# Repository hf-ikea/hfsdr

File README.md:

# https://github.com/hf-ikea/hfsdr
https://munin.uit.no/bitstream/handle/10037/19423/thesis.pdf --- ref\
https://www.analog.com/en/products/ad9641.pdf                --- main adc 14bit 80/155msps\
https://www.analog.com/en/products/ada4938-1.html            --- adc driver\
https://www.analog.com/en/products/adl5206.html              --- vga canidate\
https://www.analog.com/en/products/ad8331.html               --- vga canidate\
https://www.analog.com/en/products/ad9515.html               --- clk distrib

bpf\
vga\
antialias lpf 8th order chebyshev\
driver\
adc\
fpga fifo - lattice ecp5?\
ft60x\
usb phy

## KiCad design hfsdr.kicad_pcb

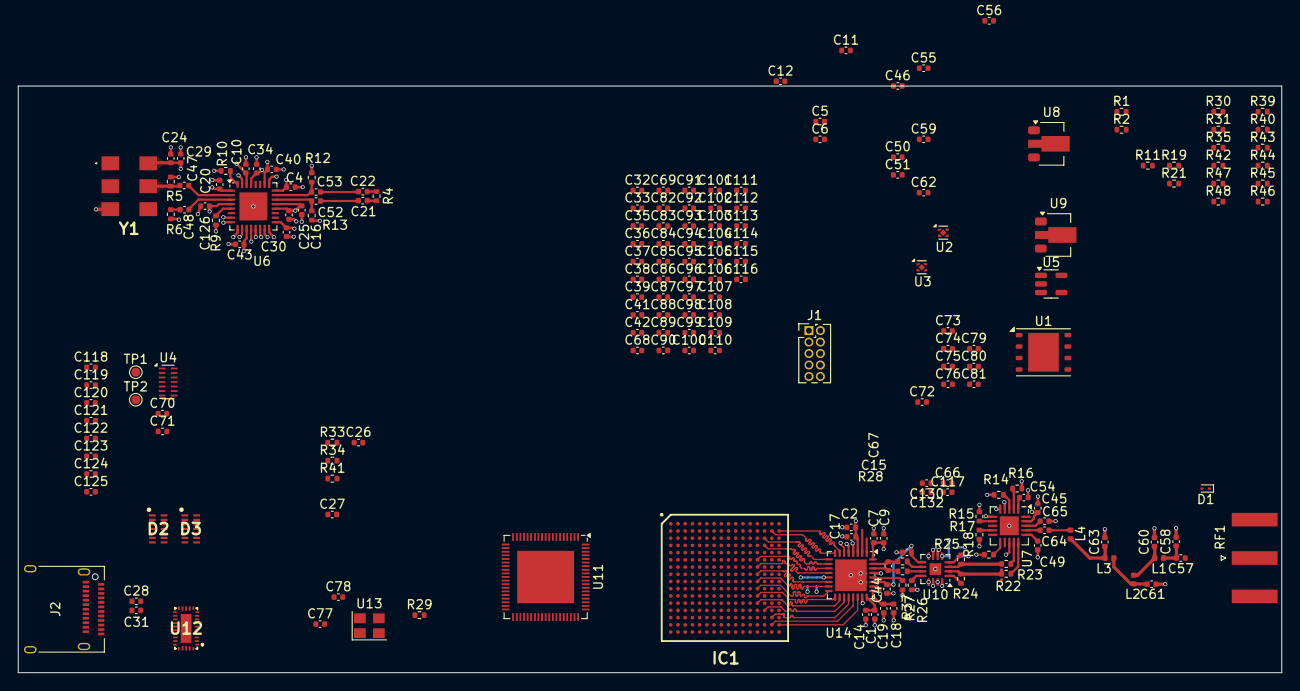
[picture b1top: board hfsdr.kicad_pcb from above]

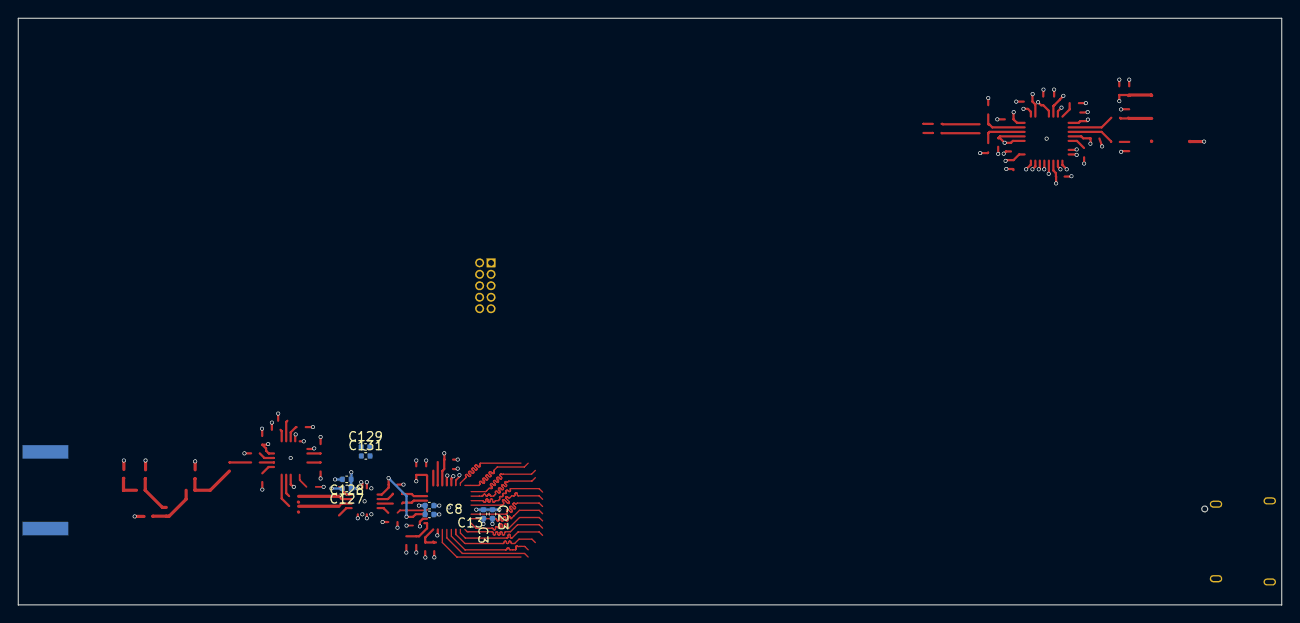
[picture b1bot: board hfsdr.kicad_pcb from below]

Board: 4 copper layers, 140.0 x 65.0 mm, 201 parts (8 on the bottom side), 170 nets.

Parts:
C1, C3, C4, C7, C10, C13, C15, C16, C17, C18, C20, C21, C22, C24, C25, C30, C34, C40, C43, C44, C45, C46, C49, C54, C79, C80, C81, C126: 0.1uF; C_0402_1005Metric
C2, C5, C6, C8, C9, C11, C12, C14, C19, C23, C29, C50, C51, C55, C59: 1uF; C_0402_1005Metric
C26, C28, C31, C70, C71, C72: 100n; C_0402_1005Metric
C27, C36, C41, C47, C48, C64, C65, C75, C76, C82, C92, C93, C94, C96, C98, C100, C102, C104, C106, C108, C110, C112, C114, C116, C117, C119, C121, C123, C125, C128, C131, C132: 0.1u; C_0402_1005Metric
C32, C33, C35, C37, C38, C39, C42, C68, C69, C83, C84, C85, C86, C87, C88, C89, C90, C91, C95, C97, C99, C101, C103, C105, C107, C109, C111, C113, C115, C118, C120, C122, C124: 10u; C_0402_1005Metric
C52, C53: 0.1n; C_0402_1005Metric
C56, C62: 2.2uF; C_0402_1005Metric
C57: 470n; C_0402_1005Metric
C58: 120p; C_0402_1005Metric
C60, C61: 200p; C_0402_1005Metric
C63: 160p; C_0402_1005Metric
C66, C127, C129, C130: 1n; C_0402_1005Metric
C67: 22pF; C_0402_1005Metric
C73: 100u; C_0402_1005Metric
C74: 4.7u; C_0402_1005Metric
C77, C78: 26p; C_0402_1005Metric
D1: ESD9B3.3ST5G; D_SOD-923
D2, D3: TPD4E05U06DQAR; SON50P135X350X55-14N
IC1: LFE5U-25F-6BG256C; BGA256C80P16X16_1400X1400X170
J1: JTAG; PinHeader_2x05_P1.27mm_Vertical
J2: GSB4D313302Y1HR; USB_C_Receptacle_Amphenol_12401610E4-2A
L1: 390n; L_0402_1005Metric
L2: 470n; L_0402_1005Metric
L3: 510n; L_0402_1005Metric
L4: 300n; L_0402_1005Metric
R1, R2, R9, R11, R14, R15, R16, R17, R18, R26, R37: 10k; R_0402_1005Metric
R4: 100; R_0402_1005Metric
R5, R6, R12, R13, R19: 50k; R_0402_1005Metric
R10: 4.12k; R_0402_1005Metric
R21: 25k; R_0402_1005Metric
R22, R23: 50; R_0402_1005Metric
R24, R25: 250; R_0402_1005Metric
R27, R28: 33; R_0402_1005Metric
R29: 1.6K 1%; R_0402_1005Metric
R30: 900k; R_0402_1005Metric
R31, R40, R43, R44, R45: 4.7k; R_0402_1005Metric
R33, R34, R41: 10K; R_0402_1005Metric
R35: 200k; R_0402_1005Metric
R39: 1.5k; R_0402_1005Metric
R42: 22; R_0402_1005Metric
R46: 120; R_0402_1005Metric
R47, R48: 0; R_0402_1005Metric
RF1: RFIN; SMA_Amphenol_132289_EdgeMount
TP1: SBU1; TestPoint_Pad_D1.0mm
TP2: SBU2; TestPoint_Pad_D1.0mm
U1: W25Q128JVP; WSON-8-1EP_6x5mm_P1.27mm_EP3.4x4.3mm
U2, U3: OnSemi_XDFN4-1EP_1.0x1.0mm_EP0.52x0.52mm
U4: TPD6E05U06RVZ; Texas_R-PUSON-N14
U5: TLV77333PDBVR; SOT-23-5
U6: AD9515; LFCSP-32-1EP_5x5mm_P0.5mm_EP3.1x3.1mm
U7: ADL5206; LFCSP-20-1EP_4x4mm_P0.5mm_EP2.1x2.1mm
U8, U9: AP2205-50Y-13; SOT-89-3
U10: ADA4938-1; LFCSP-16-1EP_3x3mm_P0.5mm_EP1.3x1.3mm
U11: FT601Q; QFN-76-1EP_9x9mm_P0.4mm_EP5.81x6.31mm
U12: HD3SS3220; HD3SS3220IRNHR
U13: ABM8-30.000MHZ-D1X-T; Oscillator_SMD_Abracon_ASE-4Pin_3.2x2.5mm
U14: AD9649; LFCSP-32-1EP_5x5mm_P0.5mm_EP3.5x3.5mm
Y1: 590BD80M0000DG

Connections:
+5V: C5.1, C6.1, C50.1, R1.1, R2.1, R11.1, U2.4 (IN), U3.4 (IN), U5.1 (IN)
+13.8V: C55.1, C59.1, U8.1 (VIN), U9.1 (VIN)
ADCIN+: C67.2, R28.2, U14.31 (VIN+)
ADCIN-: C67.1, R27.2, U14.30 (VIN-)
AGND: C1.2, C2.2, C3.2, C4.2, C5.2, C6.2, C7.2, C8.2, C9.2, C10.2, C11.2, C12.2, C13.2, C14.2, C15.2, C16.2, C17.2, C18.2, C19.2, C20.2, C23.2, C24.2, C25.2, C26.2, C27.2, C29.2, C30.2, C32.2, C33.2, C34.2, C35.2, C36.2, C37.2, C38.2, C39.2, C40.2, C41.2, C42.2, C43.2, C44.2, C45.2, C46.1, C49.2, C50.2, C51.2, C54.1, C55.2, C56.2, C58.2, C59.2, C60.2, C61.2, C62.2, C63.2, C65.1, C66.2, C68.2, C69.2, C72.1, C73.2, C74.1, C77.1, C78.1, C79.1, C80.1, C81.1, C82.2, C83.2, C84.2, C85.2, C86.2, C87.2, C88.2, C89.2, C90.2, C91.2, C92.2, C93.2, C94.2, C99.2, C100.2, C101.2, C102.2, C103.2, C104.2, C105.2, C106.2, C107.2, C108.2, C109.2, C110.2, C111.2, C112.2, C113.2, C114.2, C115.2, C116.2, C117.2, C118.2, C119.2, C120.2, C121.2, C122.2, C123.2, C124.2, C125.2, C126.2, C127.2, C128.2, C129.2, C130.2, C131.2, C132.2, D1.1 (A1), D2.3 (GND_1), D2.8 (GND_2), D3.3 (GND_1), D3.8 (GND_2), IC1.A1 (GND_1), IC1.A16 (GND_2), IC1.D2 (GND_3), IC1.D15 (GND_4), IC1.F8 (GND_5), IC1.F9 (GND_6), IC1.G8 (GND_7), IC1.G10 (GND_8), IC1.H1 (GND_9), IC1.H8 (GND_10), IC1.H9 (GND_11), IC1.H10 (GND_12), IC1.H16 (GND_13), IC1.J8 (GND_14), IC1.J9 (GND_15), IC1.J10 (GND_16), IC1.K6 (GND_17), IC1.K7 (GND_18), IC1.K8 (GND_19), IC1.K9 (GND_20), IC1.K10 (GND_21), IC1.N2 (GND_22), IC1.N10 (CFG_0), IC1.N15 (GND_23), IC1.R10 (CFG_2), IC1.T1 (GND_24), IC1.T5 (GND_25), IC1.T12 (GND_26), IC1.T16 (GND_27), J1.3 (GND), J1.5 (GND), J1.9 (GNDDetect), J2.A1 (GND), J2.A12 (GND), J2.B1 (GND), J2.B12 (GND), J2.S1 (SHIELD), R5.2, R6.1, R10.1, R12.2, R13.2, R15.1, R16.1, R17.1, R18.1, R19.2, R29.1, R31.2, R37.1, RF1.2 (Ext), U1.4 (GND), U2.2 (GND), U2.5 (EP), U3.2 (GND), U3.5 (EP), U4.5 (GND), U4.10 (GND), U5.2 (GND), U6.7 (S10), U6.8 (S9), U6.9 (S8), U6.10 (S7), U6.12 (S5), U6.13 (S4), U6.14 (S3), U6.15 (S2), U6.16 (S1), U6.25 (S0), U6.31 (GND), U6.33 (GND), U7.21 (EP), U8.2 (GND), U9.2 (GND), U10.13 (V-), U10.14 (V-), U10.15 (V-), U10.16 (V-), U10.17 (PAD), U11.1 (GND), U11.26 (GND), U11.29 (GND), U11.36 (GND), U11.77 (GND), U12.13 (GND), U12.28 (GND), U12.31 (EP), U13.2 (GND), U13.4 (GND), U14.26 (SENSE), U14.33 (EP), Y1.3 (GND)
AMPIN+: C64.2, U7.17 (VIN+)
AMPIN-: C65.2, U7.18 (VIN-)
AVDD: C1.1, C2.1, C7.1, C8.1, C9.1, C11.1, C13.1, C14.1, C17.1, U2.1 (OUT), U14.3 (AVDD), U14.24 (AVDD), U14.29 (AVDD), U14.32 (AVDD)
CC1: R47.2, U4.1 (NC), U4.14 (D1+), U12.2 (CC1)
CC2: R48.2, U4.2 (NC), U4.13 (D1-), U12.1 (CC2)
CLK+: C22.2, R4.2, U14.1 (CLK+)
CLK-: C21.2, R4.1, U14.2 (CLK-)
CLKVDD: C4.1, C10.1, C16.1, C20.1, C24.1, C25.1, C29.1, C30.1, C34.1, C40.1, C43.1, C46.2, C51.1, C126.1, R9.2, U5.5 (OUT), U6.1 (VS), U6.4 (VS), U6.11 (S6), U6.17 (VS), U6.20 (VS), U6.21 (VS), U6.24 (VS), U6.26 (VS), U6.29 (VS), U6.30 (VS), Y1.6 (VDD)
CSBU1: J2.A8 (SBU1), TP1.1, U4.7 (NC), U4.8 (D3-)
CSBU2: J2.B8 (SBU2), TP2.1, U4.6 (NC), U4.9 (D3+)
C_CC1: J2.A5 (CC1), R47.1
C_CC2: J2.B5 (CC2), R48.1
D0: IC1.B16 (PR2A), U14.7 (D0)
D1: IC1.B15 (PR2B), U14.8 (D1)
D2: IC1.C14 (PR2C), U14.9 (D2)
D3: IC1.D14 (PR2D), U14.10 (D3)
D4: IC1.F13 (PR8C), U14.11 (D4)
D5: IC1.G13 (PR11B), U14.12 (D5)
D6: IC1.H13 (PR17B), U14.14 (D6)
D7: IC1.J13 (PR17C), U14.15 (D7)
D8: IC1.K13 (PR29A), U14.16 (D8)
D9: IC1.L13 (PR29C), U14.17 (D9)
D10: IC1.M13 (PR35C), U14.18 (D10)
D11: IC1.N14 (PR35D), U14.19 (D11)
D12: IC1.P15 (PR32B), U14.20 (D12)
D13: IC1.R15 (PR38C), U14.21 (D13)
D+: J2.A6 (D+), J2.B6 (D+), U4.4 (NC), U4.11 (D2-), U11.23 (DP)
D-: J2.A7 (D-), J2.B7 (D-), U4.3 (NC), U4.12 (D2+), U11.25 (DM)
DCO: IC1.R16 (PR35B), U14.22 (DCO)
DRIVER_VDD: C62.1, C66.1, C117.1, C127.1, C128.1, C129.1, C130.1, C131.1, C132.1, R26.2, U9.3 (VOUT), U10.5 (V+), U10.6 (V+), U10.7 (V+), U10.8 (V+)
DRVDD: C3.1, C12.1, C23.1, C99.1, C100.1, C101.1, C102.1, C103.1, C104.1, C105.1, C106.1, IC1.H11 (VCCIO2_1), IC1.J11 (VCCIO2_2), IC1.K11 (VCCIO3_1), IC1.L11 (VCCIO3_2), U3.1 (OUT), U14.13 (DRVDD)
EN_MUX: IC1.B5 (PT15B), U12.12 (ENn_MUX)
FPGA_RESET: IC1.M8 (PB15B), IC1.R9 (PROGRAMN), J1.10 (~RESET)
FT_BE0: IC1.T2 (PL38D), U11.4 (BE_0)
FT_BE1: IC1.T3 (PL41D), U11.5 (BE_1)
FT_BE2: IC1.R1 (PL35B), U11.6 (BE_2)
FT_BE3: IC1.P1 (PL35A), U11.7 (BE_3)
FT_D0: IC1.R3 (PL41B), U11.40 (DATA_0)
FT_D1: IC1.R2 (PL38C), U11.41 (DATA_1)
FT_D2: IC1.P2 (PL32B), U11.42 (DATA_2)
FT_D3: IC1.N1 (PL32A), U11.43 (DATA_3)
FT_D4: IC1.N3 (PL35D), U11.44 (DATA_4)
FT_D5: IC1.M3 (PL32D), U11.45 (DATA_5)
FT_D6: IC1.M2 (PL26D), U11.46 (DATA_6)
FT_D7: IC1.M1 (PL26C), U11.47 (DATA_7)
FT_D8: IC1.L3 (PL32C), U11.50 (DATA_8)
FT_D9: IC1.L2 (PL26B), U11.51 (DATA_9)
FT_D10: IC1.L1 (PL26A), U11.52 (DATA_10)
FT_D11: IC1.K3 (PL20D), U11.53 (DATA_11)
FT_D12: IC1.K2 (PL23D), U11.54 (DATA_12)
FT_D13: IC1.K1 (PL23C), U11.55 (DATA_13)
FT_D14: IC1.J3 (PL20C), U11.56 (DATA_14)
FT_D15: IC1.J2 (PL23B), U11.57 (DATA_15)
FT_D16: IC1.J1 (PL23A), U11.60 (DATA_16)
FT_D17: IC1.H3 (PL14D), U11.61 (DATA_17)
FT_D18: IC1.H2 (PL20B), U11.62 (DATA_18)
FT_D19: IC1.G3 (PL14C), U11.63 (DATA_19)
FT_D20: IC1.G2 (PL14B), U11.64 (DATA_20)
FT_D21: IC1.G1 (PL20A), U11.65 (DATA_21)
FT_D22: IC1.F3 (PL5D), U11.66 (DATA_22)
FT_D23: IC1.F2 (PL11C), U11.67 (DATA_23)
FT_D24: IC1.F1 (PL14A), U11.69 (DATA_24)
FT_D25: IC1.E3 (PL5C), U11.70 (DATA_25)
FT_D26: IC1.E2 (PL8B), U11.71 (DATA_26)
FT_D27: IC1.E1 (PL11D), U11.72 (DATA_27)
FT_D28: IC1.D3 (PL2D), U11.73 (DATA_28)
FT_D29: IC1.D1 (PL8A), U11.74 (DATA_29)
FT_D30: IC1.C3 (PL2C), U11.75 (DATA_30)
FT_D31: IC1.C2 (PL5B), U11.76 (DATA_31)
FT_RESETn: C26.1, R34.1, U11.15 (~RESET)
FT_SIWUn: R33.1, U11.10 (~SIWU)
FT_WAKEUPn: R41.1, U11.16 (~WAKEUP)
JTAG_TCK: IC1.T10 (TCK), J1.4 (SWCLK/TCK)
JTAG_TDI: IC1.R11 (TDI), J1.8 (NC/TDI), R45.1
JTAG_TDO: IC1.M10 (TDO), J1.6 (SWO/TDO), R44.1
JTAG_TMS: IC1.T11 (TMS), J1.2 (SWDIO/TMS), R43.1
MUX_ENn_CC: IC1.E4 (PT9A), U12.29 (ENn_CC)
MUX_I2C_ADDR: IC1.C5 (PT15A), U12.22 (ADDR)
MUX_I2C_INTR: IC1.D5 (PT13B), U12.23 (INT_N/OUT3)
MUX_SCL: IC1.C4 (PT11A), U12.26 (SCL/OUT2)
MUX_SDA: IC1.B4 (PT11B), U12.25 (SDA/OUT1)
MUX_USB_ID: IC1.D4 (PT9B), U12.27 (ID)
unnamed: C21.1, C52.2
unnamed: C22.1, C53.2
unnamed: C57.2, C58.1, L1.1
unnamed: C60.1, L1.2, L2.1
unnamed: C61.1, L2.2, L3.1
unnamed: C63.1, L3.2, L4.1
unnamed: C64.1, L4.2
unnamed: C95.2, C96.2, C97.2, C98.2
unnamed: C57.1, D1.2 (A2), RF1.1 (In)
unnamed: C95.1, C96.1, C97.1, C98.1, IC1.G11 (VCCAUX_1), IC1.L7 (VCCAUX_2), R46.2
unnamed: R27.1, U10.11
unnamed: R28.1, U10.10
unnamed: R1.2, U2.3 (EN)
unnamed: R2.2, U3.3 (EN)
unnamed: R11.2, U5.3 (EN)
unnamed: C47.2, U6.2 (CLK)
unnamed: C48.2, U6.3 (CLKB)
unnamed: C53.1, R12.1, U6.23 (OUT0)
unnamed: C52.1, R13.1, U6.22 (OUT0B)
unnamed: R10.2, U6.32 (RSET)
unnamed: R9.1, U6.5 (SYNCB)
unnamed: R19.1, R21.2, U7.20 (DNC_INTERIM)
unnamed: R15.2, U7.7 (FA/GS0/D2)
unnamed: R18.2, U7.11 (LATCH/SPI_HP_LP)
unnamed: R14.2, U7.3 (MODE0)
unnamed: R16.2, U7.2 (MODE1)
unnamed: R17.2, U7.9 (UPDN_DAT/D0/3SPI_4SPI)
unnamed: C54.2, U7.1 (VCM)
unnamed: R22.1, U7.15 (VOUT+)
unnamed: R23.1, U7.14 (VOUT-)
unnamed: R22.2, R24.1, U10.2 (+)
unnamed: R23.2, R25.1, U10.3 (-)
unnamed: R25.2, U10.4 (FB+)
unnamed: R24.2, U10.1 (FB-)
unnamed: R26.1, U10.12 (~PD)
unnamed: C74.2, U11.2 (AVDD), U11.3 (VD10), U11.30 (VD10), U11.33 (VD10), U11.39 (DV10), U11.48 (VD10)
unnamed: R42.1, U11.58 (CLK)
unnamed: U11.34 (RIDN), U12.10 (RXn)
unnamed: U11.35 (RIDP), U12.9 (RXp)
unnamed: R29.2, U11.27 (RREF)
unnamed: C75.2, U11.31 (TODN)
unnamed: C76.2, U11.32 (TODP)
unnamed: C77.2, U11.21 (XI), U13.1 (XI)
unnamed: C78.2, U11.22 (XO), U13.3 (XO)
unnamed: R31.1, U12.4 (PORT)
unnamed: C75.1, U12.7 (TXn)
unnamed: C76.1, U12.6 (TXp)
unnamed: R30.1, U12.5 (VBUS_DET)
unnamed: R37.2, U14.28 (RBIAS)
unnamed: C48.1, R6.2, Y1.4 (CLK+)
unnamed: C47.1, R5.1, Y1.5 (CLK-)
P1.1V: C32.1, C33.1, C35.1, C36.1, C37.1, C38.1, C39.1, C41.1, C42.1, C68.1, C69.1, C82.1, C83.1, C84.1, C85.1, C86.1, C87.1, C88.1, C89.1, C90.1, C91.1, C92.1, C93.1, C94.1, IC1.G6 (VCC_1), IC1.G7 (VCC_2), IC1.G9 (VCC_3), IC1.L8 (VCC_4), IC1.L9 (VCC_5), IC1.L10 (VCC_6)
P3.3V: C27.1, C107.1, C108.1, C109.1, C110.1, C111.1, C112.1, C113.1, C114.1, C115.1, C116.1, C118.1, C119.1, C120.1, C121.1, C122.1, C123.1, C124.1, C125.1, IC1.F6 (VCCIO0_1), IC1.F7 (VCCIO0_2), IC1.F10 (VCCIO1_1), IC1.F11 (VCCIO1_2), IC1.H6 (VCCIO7_1), IC1.H7 (VCCIO7_2), IC1.J6 (VCCIO6_1), IC1.J7 (VCCIO6_2), IC1.L6 (VCCIO8), IC1.P10 (CFG_1), J1.1 (VTref), R39.2, R40.2, R43.2, R44.2, R45.2, U1.8 (VCC)
PORT_DIR: IC1.A5 (PT18A), R35.2, U12.11 (DIR)
QSPI_D2: IC1.M7 (PB9B), U1.3 (IO2)
QSPI_D3: IC1.N7 (PB9A), U1.7 (IO3)
RX1+: D2.5 (D2-), D2.6 (NC_1), J2.B11 (RX1+), U12.15 (RX1p)
RX1-: D2.4 (D2+), D2.7 (NC_2), J2.B10 (RX1-), U12.14 (RX1n)
RX2+: D3.5 (D2-), D3.6 (NC_1), J2.A11 (RX2+), U12.19 (RX2p)
RX2-: D3.4 (D2+), D3.7 (NC_2), J2.A10 (RX2-), U12.18 (RX2n)
SPICFG_MISO: IC1.T7 (PB11A), U1.2 (DO(IO1))
SPICFG_MOSI: IC1.T8 (PB11B), U1.5 (DI(IO0))
SPICFG_SCK: IC1.N9 (CCLK/MCLK/SCK), R39.1, U1.6 (CLK)
SPICFG_SS: IC1.N8 (PB15A), R40.1, U1.1 (~CS)
TX1+: C28.1, D2.2 (D1-), D2.9 (NC_3), J2.A2 (TX1+)
TX1-: C31.1, D2.1 (D1+), D2.10 (NC_4), J2.A3 (TX1-)
TX1N: C28.2, U12.16 (TX1n)
TX1P: C31.2, U12.17 (TX1p)
TX2+: C71.1, D3.2 (D1-), D3.9 (NC_3), J2.B2 (TX2+)
TX2-: C70.1, D3.1 (D1+), D3.10 (NC_4), J2.B3 (TX2-)
TX2N: C70.2, U12.20 (TX2n)
TX2P: C71.2, U12.21 (TX2p)
VBUS: C73.1, J2.A4 (VBUS), J2.A9 (VBUS), J2.B4 (VBUS), J2.B9 (VBUS), R30.2, U11.37 (VBUS)
VCC_3.3V: C79.2, C80.2, C81.2, R33.2, R34.2, R35.1, R41.2, U11.14 (VCCIO), U11.20 (VCC33), U11.24 (VCC33), U11.28 (VDDA), U11.38 (VCC33), U11.49 (VCCIO), U11.59 (VCCIO), U11.68 (VCCIO), U12.8 (VCC33)
VCC_5V: C72.2, U12.30 (VDD5)
VCM: C15.1, C44.1, U10.9 (V_{OCM}), U14.27 (VCM)
VCONN_FAULT: IC1.E5 (PT13A), U12.24 (VCONN_FAULT_N)
VGA_CSB: IC1.A2 (PT4A), U7.6 (CS/GS1/D3)
VGA_ENABLE: IC1.A4 (PT6B), U7.13 (PWUP)
VGA_SCLK: IC1.B3 (PT4B), U7.5 (SCLK/D4)
VGA_SDIO: IC1.A3 (PT6A), U7.4 (SDIO/SDO)
VGA_VDD: C45.1, C49.1, C56.1, R14.1, R21.1, U7.16 (VPOS), U7.19 (VPOS), U8.3 (VOUT)
VREF: C18.1, C19.1, U14.25 (VREF)

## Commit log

2025-02-07 hres
2025-02-07 readme
2025-02-07 wokrin
2025-02-07 add .gitignore
2025-02-08 pcb ready
2025-02-08 dgfsd
2025-02-11 setup usbc
2025-02-11 setup devenv proper for ecp5
2025-02-12 begin fpga work
2025-02-13 i swear im just 'importing' libraries
2025-02-13 nope not doing jesd
2025-02-13 adc crashout complete
2025-02-14 whatever man
2025-02-14 dawg idk
2025-02-14 add default make target
2025-02-14 some more fpga work
2025-02-15 i dont even remember what i did
2025-02-15 some moderate pcb work
2025-02-16 i forgot
2025-02-16 dac work
